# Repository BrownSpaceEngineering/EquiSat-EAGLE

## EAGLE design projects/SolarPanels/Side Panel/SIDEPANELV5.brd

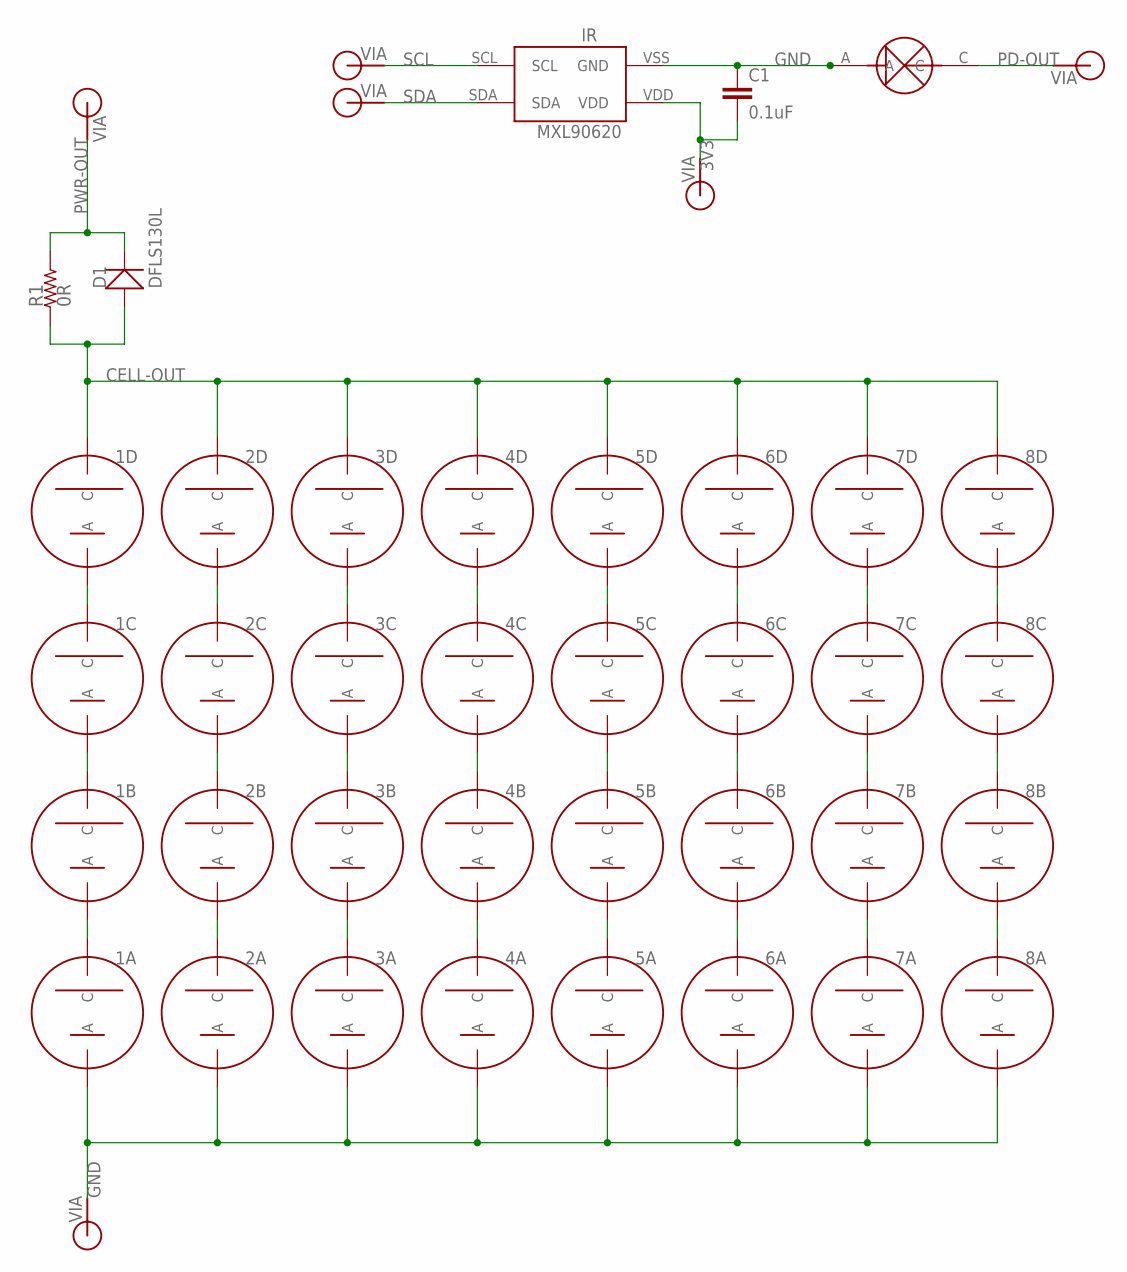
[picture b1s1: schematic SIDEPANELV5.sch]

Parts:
1A, 1B, 1C, 1D, 2A, 2B, 2C, 2D, 3A, 3B, 3C, 3D, 4A, 4B, 4C, 4D, 5A, 5B, 5C, 5D, 6A, 6B, 6C, 6D, 7A, 7B, 7C, 7D, 8A, 8B, 8C, 8D: SOLARCELLV3; TRISOLX-V3
3V3: VIA60MIL-SQ; VIA-60MIL-SQ
C1: 0.1uF; 0805
D1: DFLS130L; PWRDI-123
GND: VIA60MIL-SQ; VIA-60MIL-SQ
IR: MXL90620
PD: PHOTODETECTOR; PHOTODECTORDEVICE2
PD-OUT: VIA60MIL-SQ; VIA-60MIL-SQ
PWR-OUT: VIA60MIL-SQ; VIA-60MIL-SQ
R1: 0R; 1210
SCL: VIA60MIL-SQ; VIA-60MIL-SQ
SDA: VIA60MIL-SQ; VIA-60MIL-SQ

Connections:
3V3: 3V3.P$1, C1.2, IR.VDD
CELL-OUT: 1D.CATHODE (C), 2D.CATHODE (C), 3D.CATHODE (C), 4D.CATHODE (C), 5D.CATHODE (C), 6D.CATHODE (C), 7D.CATHODE (C), 8D.CATHODE (C), D1.A, R1.P$1 (1)
GND: 1A.ANODE (A), 2A.ANODE (A), 3A.ANODE (A), 4A.ANODE (A), 5A.ANODE (A), 6A.ANODE (A), 7A.ANODE (A), 8A.ANODE (A), C1.1, GND.P$1, IR.VSS (GND), PD.A
unnamed: 2C.CATHODE (C), 2D.ANODE (A)
unnamed: 1C.CATHODE (C), 1D.ANODE (A)
unnamed: 1B.CATHODE (C), 1C.ANODE (A)
unnamed: 1A.CATHODE (C), 1B.ANODE (A)
unnamed: 2B.CATHODE (C), 2C.ANODE (A)
unnamed: 2A.CATHODE (C), 2B.ANODE (A)
unnamed: 3C.CATHODE (C), 3D.ANODE (A)
unnamed: 3B.CATHODE (C), 3C.ANODE (A)
unnamed: 3A.CATHODE (C), 3B.ANODE (A)
unnamed: 4C.CATHODE (C), 4D.ANODE (A)
unnamed: 4B.CATHODE (C), 4C.ANODE (A)
unnamed: 4A.CATHODE (C), 4B.ANODE (A)
unnamed: 5C.CATHODE (C), 5D.ANODE (A)
unnamed: 5B.CATHODE (C), 5C.ANODE (A)
unnamed: 5A.CATHODE (C), 5B.ANODE (A)
unnamed: 6C.CATHODE (C), 6D.ANODE (A)
unnamed: 6B.CATHODE (C), 6C.ANODE (A)
unnamed: 6A.CATHODE (C), 6B.ANODE (A)
unnamed: 7C.CATHODE (C), 7D.ANODE (A)
unnamed: 7B.CATHODE (C), 7C.ANODE (A)
unnamed: 7A.CATHODE (C), 7B.ANODE (A)
unnamed: 8C.CATHODE (C), 8D.ANODE (A)
unnamed: 8B.CATHODE (C), 8C.ANODE (A)
unnamed: 8A.CATHODE (C), 8B.ANODE (A)
PD-OUT: PD.C, PD-OUT.P$1
PWR-OUT: D1.C, PWR-OUT.P$1, R1.P$2 (2)
SCL: IR.SCL, SCL.P$1
SDA: IR.SDA, SDA.P$1

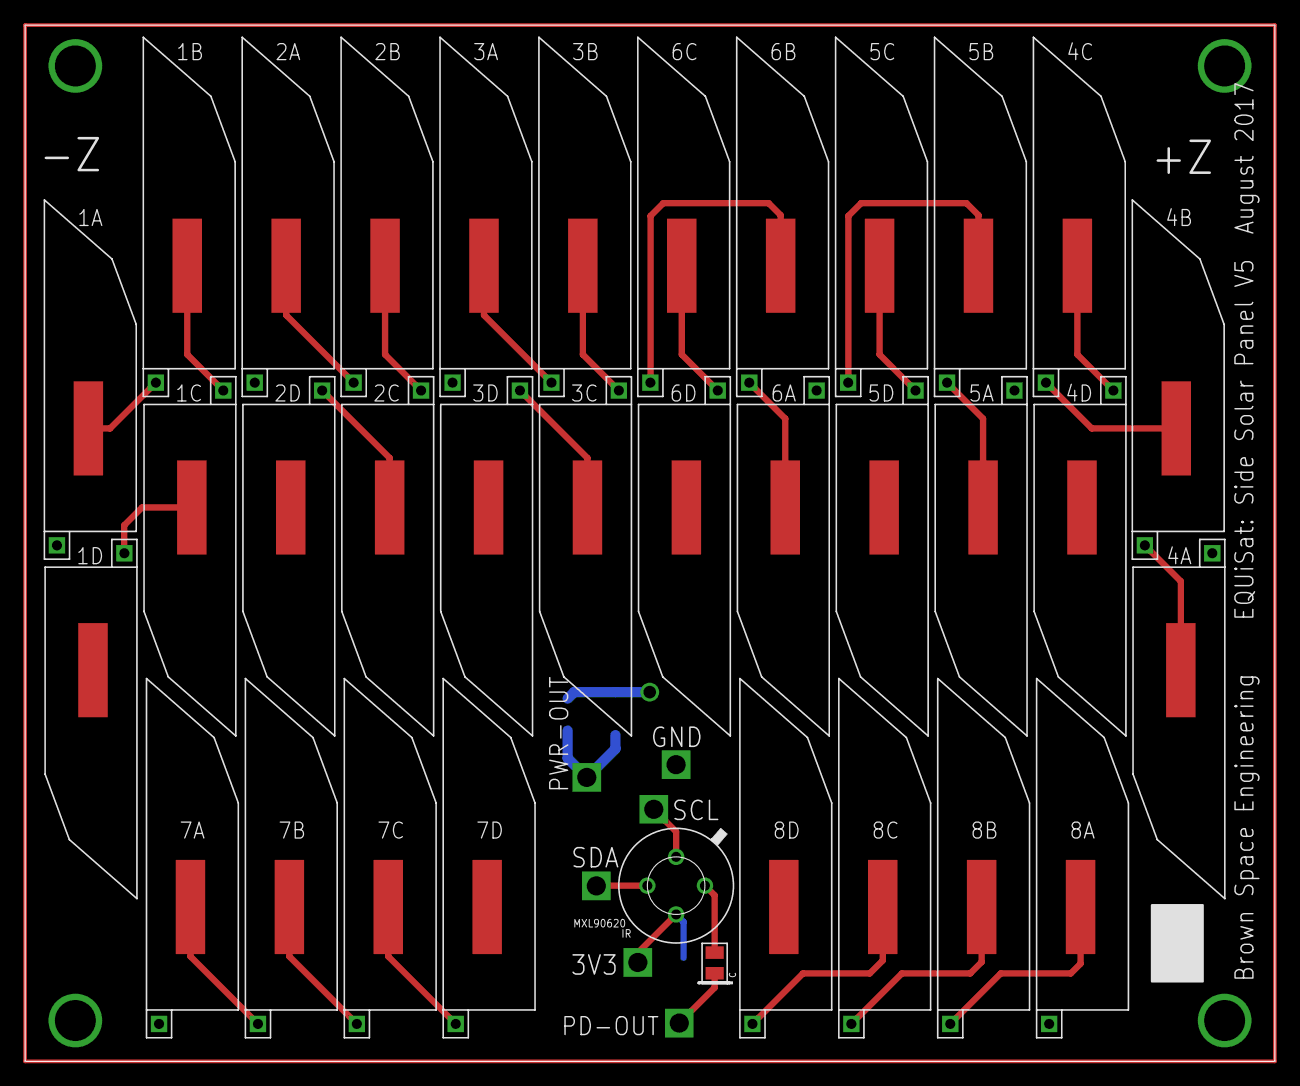
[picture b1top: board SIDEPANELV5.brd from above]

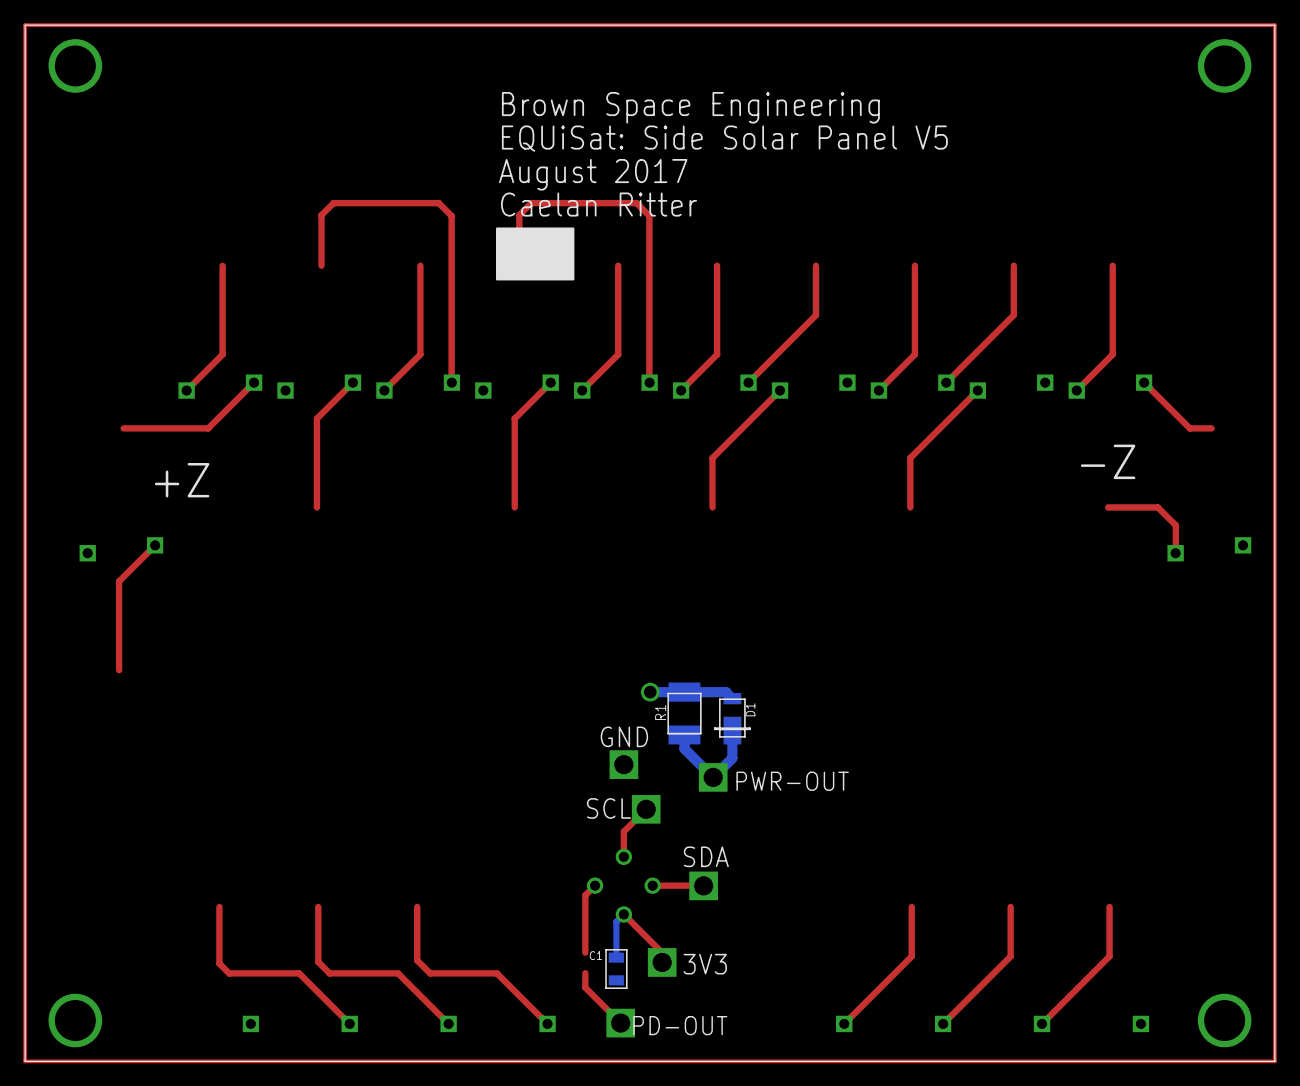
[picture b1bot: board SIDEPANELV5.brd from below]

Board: 2 copper layers, 99.5 x 82.5 mm, 43 parts (3 on the bottom side), 31 nets.

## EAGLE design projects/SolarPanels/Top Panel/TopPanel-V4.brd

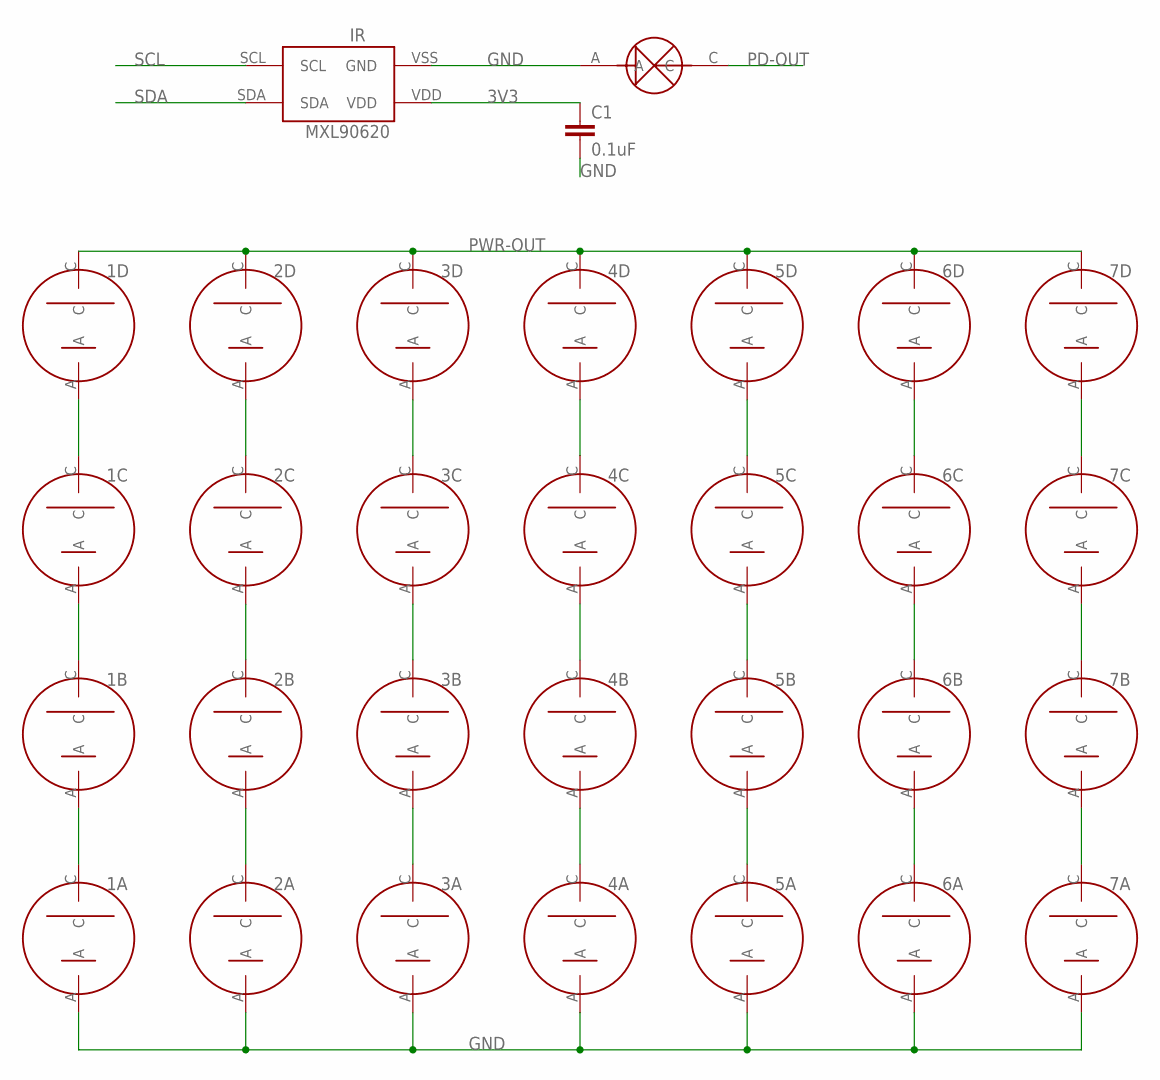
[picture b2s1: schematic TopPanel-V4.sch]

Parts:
1A, 1B, 1C, 1D, 2A, 2B, 2C, 2D, 3A, 3B, 3C, 3D, 4A, 4B, 4C, 4D, 5A, 5B, 5C, 5D, 6A, 6B, 6C, 6D, 7A, 7B, 7C, 7D: NEWSOLARPANEL; SOLARCELL2
C1: 0.1uF; 0805
IR: MXL90620
PD: PHOTODETECTOR; PHOTODECTORDEVICE2

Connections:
2D: 2C.C, 2D.A
3V3: C1.1, IR.VDD
GND: 1A.A, 2A.A, 3A.A, 4A.A, 5A.A, 6A.A, 7A.A, C1.2, IR.VSS (GND), PD.A
unnamed: 1A.C, 1B.A
unnamed: 1B.C, 1C.A
unnamed: 1C.C, 1D.A
unnamed: 7A.C, 7B.A
unnamed: 7B.C, 7C.A
unnamed: 2A.C, 2B.A
unnamed: 2B.C, 2C.A
unnamed: 7C.C, 7D.A
unnamed: 3A.C, 3B.A
unnamed: 3B.C, 3C.A
unnamed: 3C.C, 3D.A
unnamed: 4A.C, 4B.A
unnamed: 4B.C, 4C.A
unnamed: 4C.C, 4D.A
unnamed: 5A.C, 5B.A
unnamed: 5B.C, 5C.A
unnamed: 5C.C, 5D.A
unnamed: 6A.C, 6B.A
unnamed: 6B.C, 6C.A
unnamed: 6C.C, 6D.A
PD-OUT: PD.C
PWR-OUT: 1D.C, 2D.C, 3D.C, 4D.C, 5D.C, 6D.C, 7D.C
SCL: IR.SCL
SDA: IR.SDA

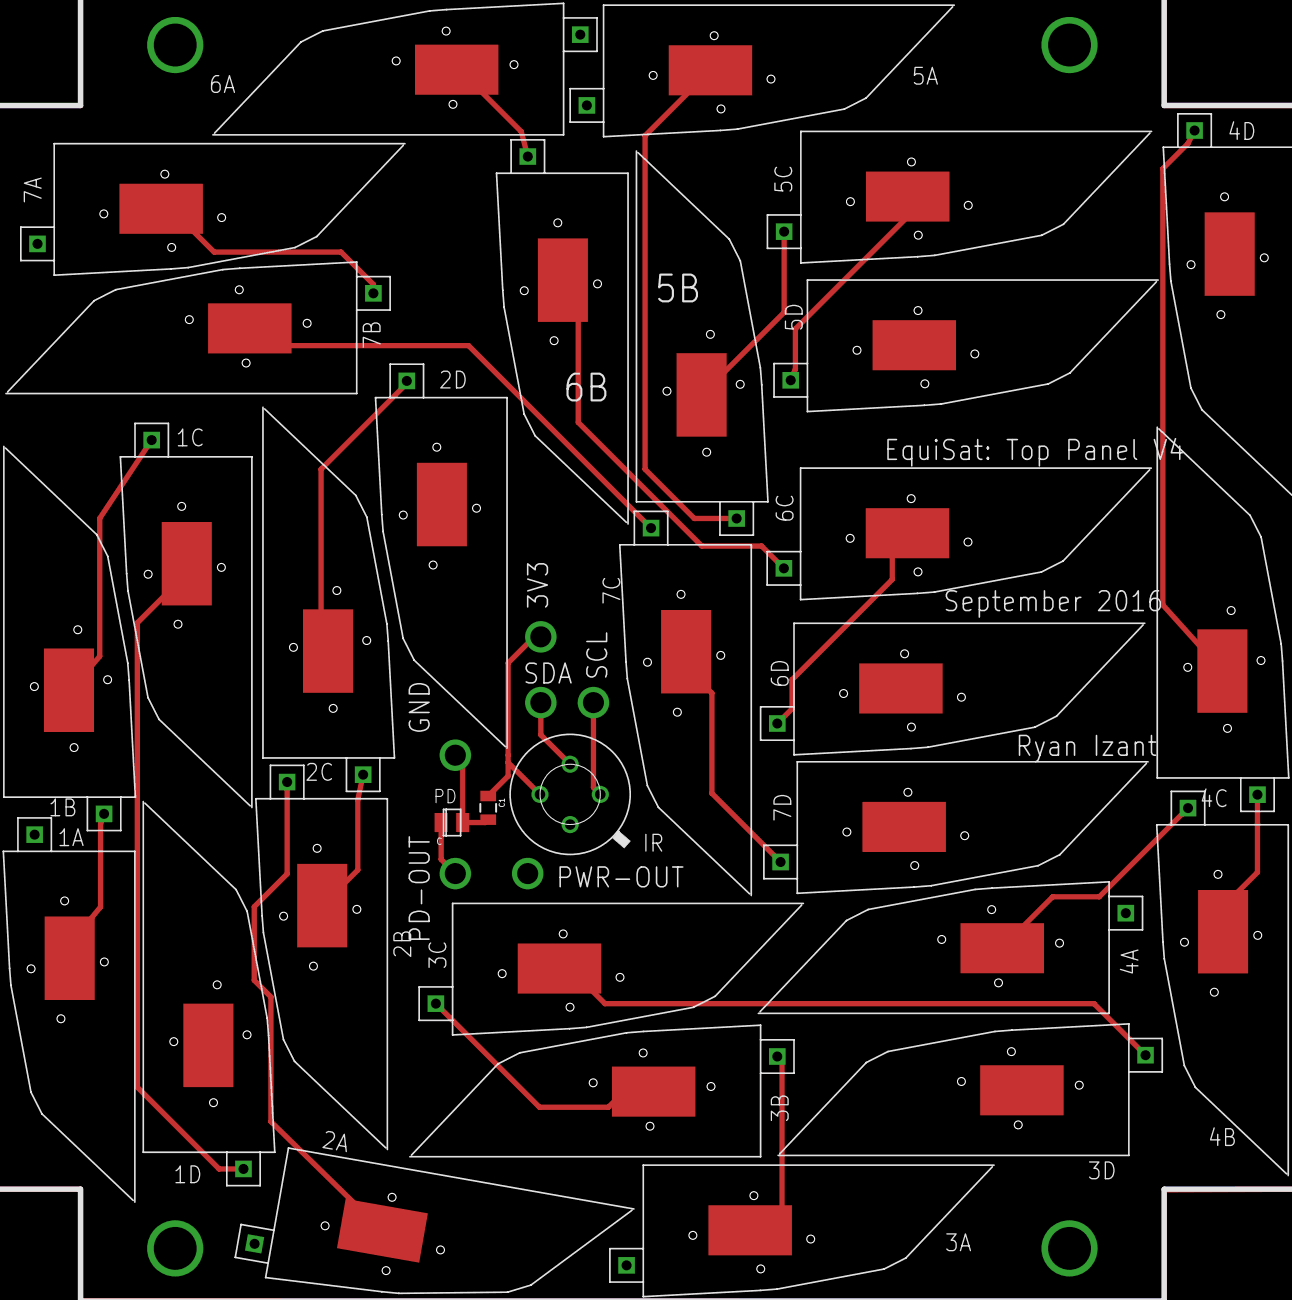
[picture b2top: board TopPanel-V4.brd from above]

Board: 2 copper layers, 31 parts (0 on the bottom side), 24 nets.

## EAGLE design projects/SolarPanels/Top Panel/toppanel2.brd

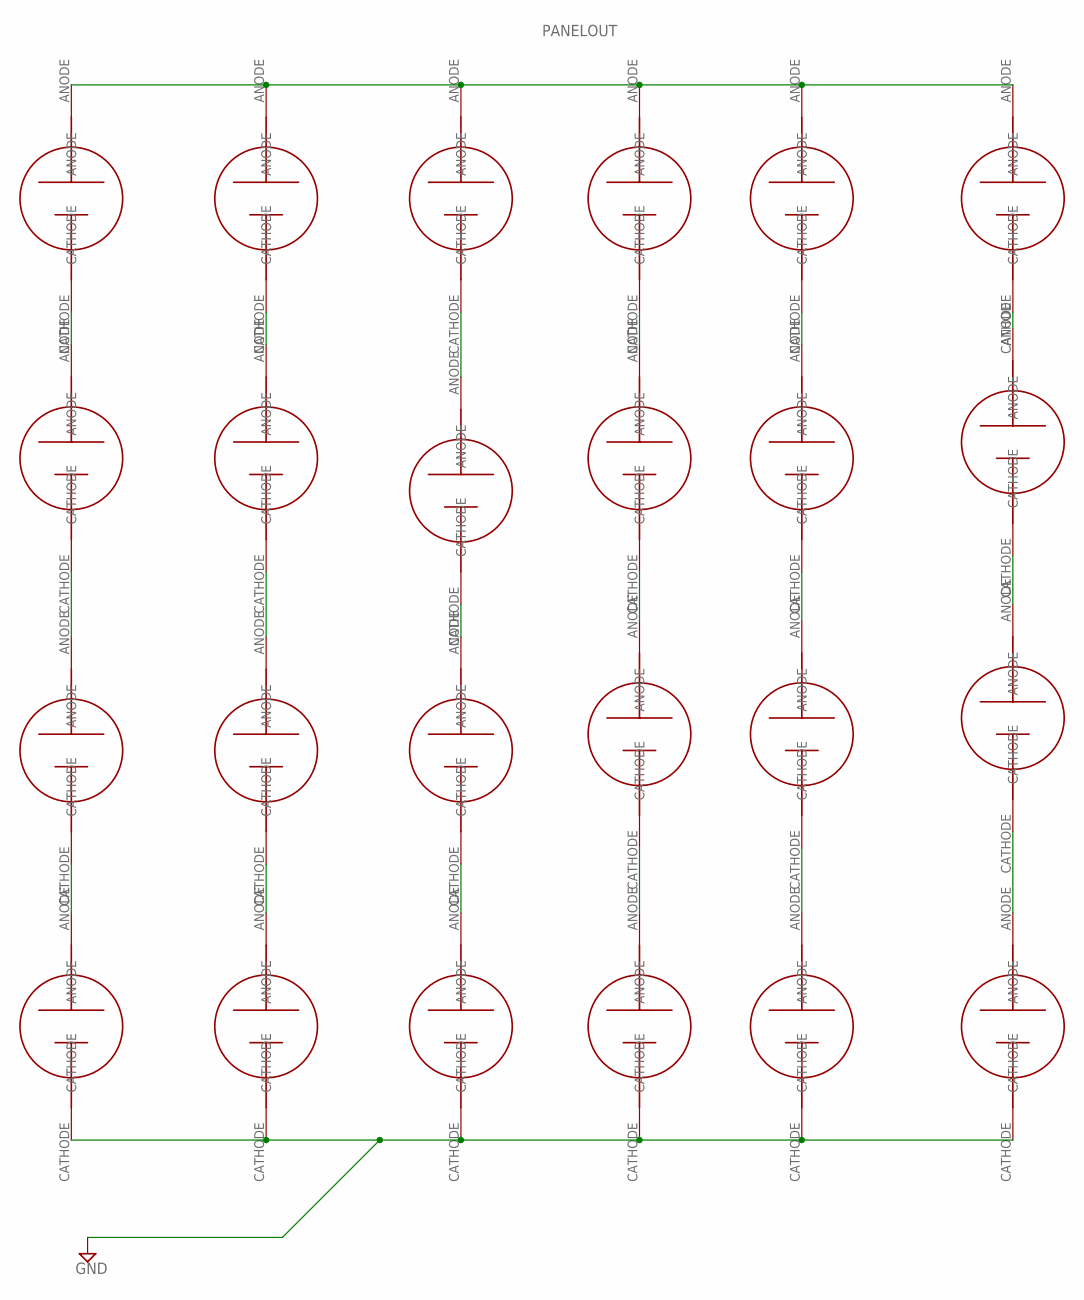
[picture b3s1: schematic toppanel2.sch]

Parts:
1A, 1B, 1C, 1D, 2A, 2B, 2C, 2D, 3A, 3B, 3C, 3D, 4A, 4B, 4C, 4D, 5A, 5B, 5C, 5D, 6A, 6B, 6C, 6D: SOLARCELL

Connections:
GND: 1A.CATHODE, 2A.CATHODE, 3A.CATHODE, 4A.CATHODE, 5A.CATHODE, 6A.CATHODE
unnamed: 1C.ANODE, 1D.CATHODE
unnamed: 1B.ANODE, 1C.CATHODE
unnamed: 1A.ANODE, 1B.CATHODE
unnamed: 2C.ANODE, 2D.CATHODE
unnamed: 2B.ANODE, 2C.CATHODE
unnamed: 2A.ANODE, 2B.CATHODE
unnamed: 3C.ANODE, 3D.CATHODE
unnamed: 3B.ANODE, 3C.CATHODE
unnamed: 3A.ANODE, 3B.CATHODE
unnamed: 4C.ANODE, 4D.CATHODE
unnamed: 4B.ANODE, 4C.CATHODE
unnamed: 4A.ANODE, 4B.CATHODE
unnamed: 5C.ANODE, 5D.CATHODE
unnamed: 5B.ANODE, 5C.CATHODE
unnamed: 5A.ANODE, 5B.CATHODE
unnamed: 6C.ANODE, 6D.CATHODE
unnamed: 6B.ANODE, 6C.CATHODE
unnamed: 6A.ANODE, 6B.CATHODE
PANELOUT: 1D.ANODE, 2D.ANODE, 3D.ANODE, 4D.ANODE, 5D.ANODE, 6D.ANODE

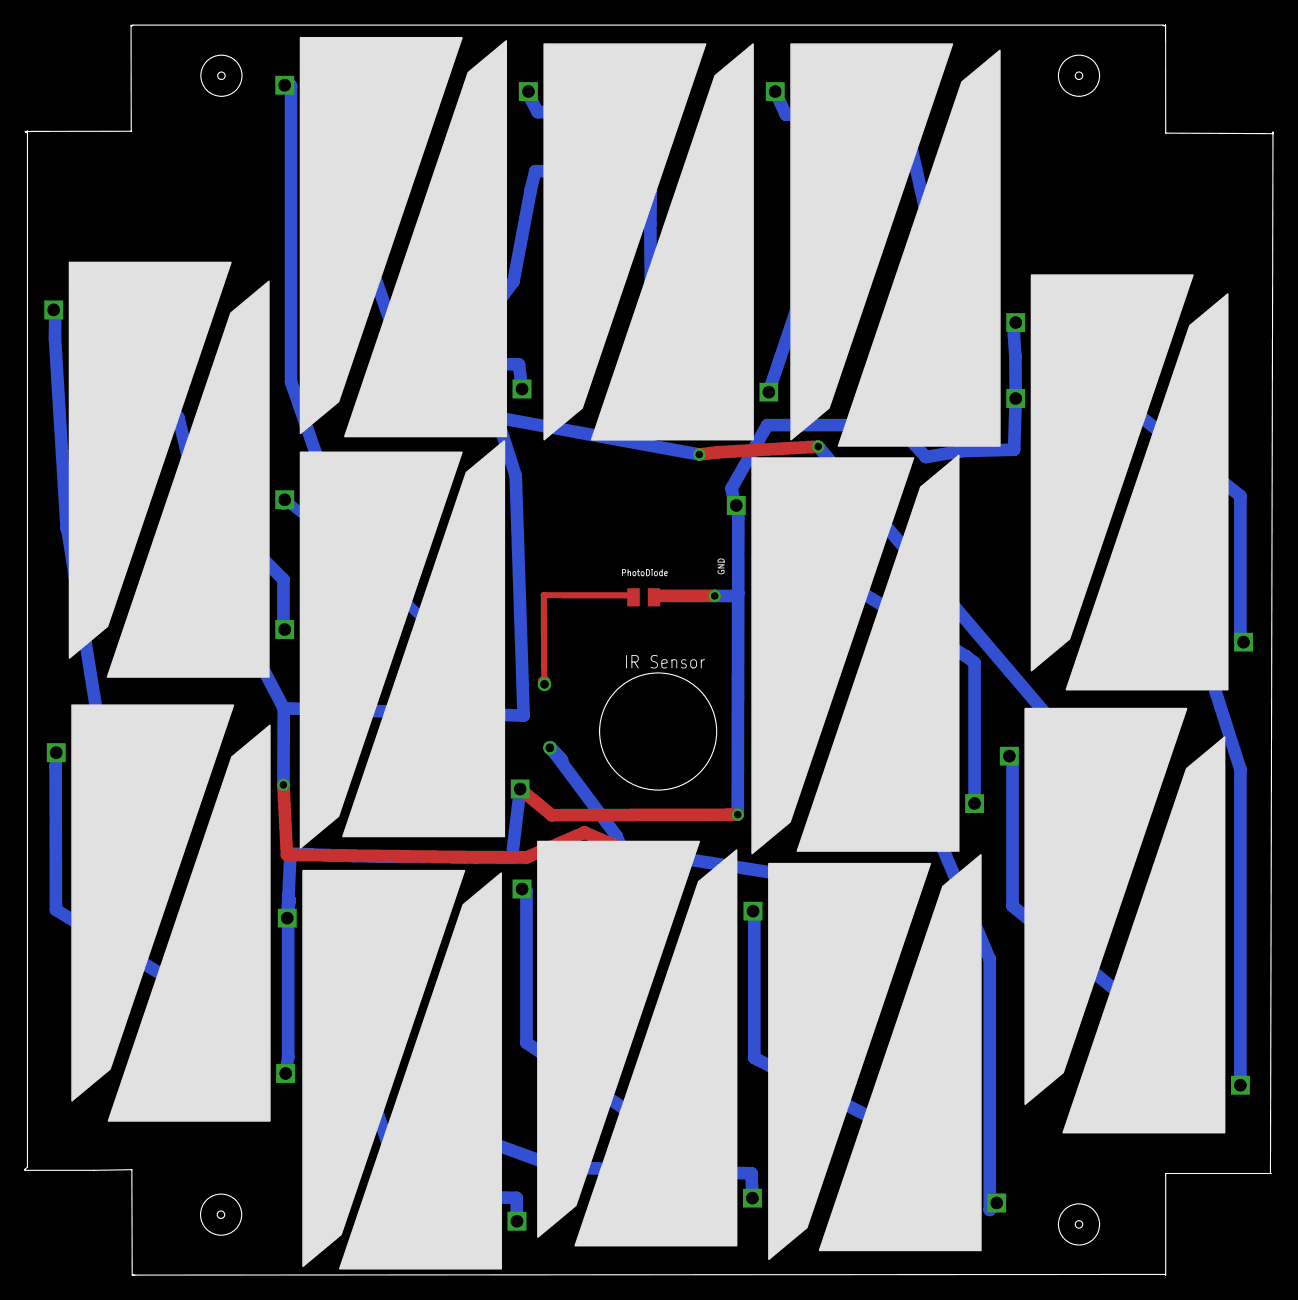
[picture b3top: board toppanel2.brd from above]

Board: 2 copper layers, 100.2 x 100.3 mm, 25 parts (0 on the bottom side), 20 nets.

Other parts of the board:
E$1: PHOTODECTORDEVICE2
